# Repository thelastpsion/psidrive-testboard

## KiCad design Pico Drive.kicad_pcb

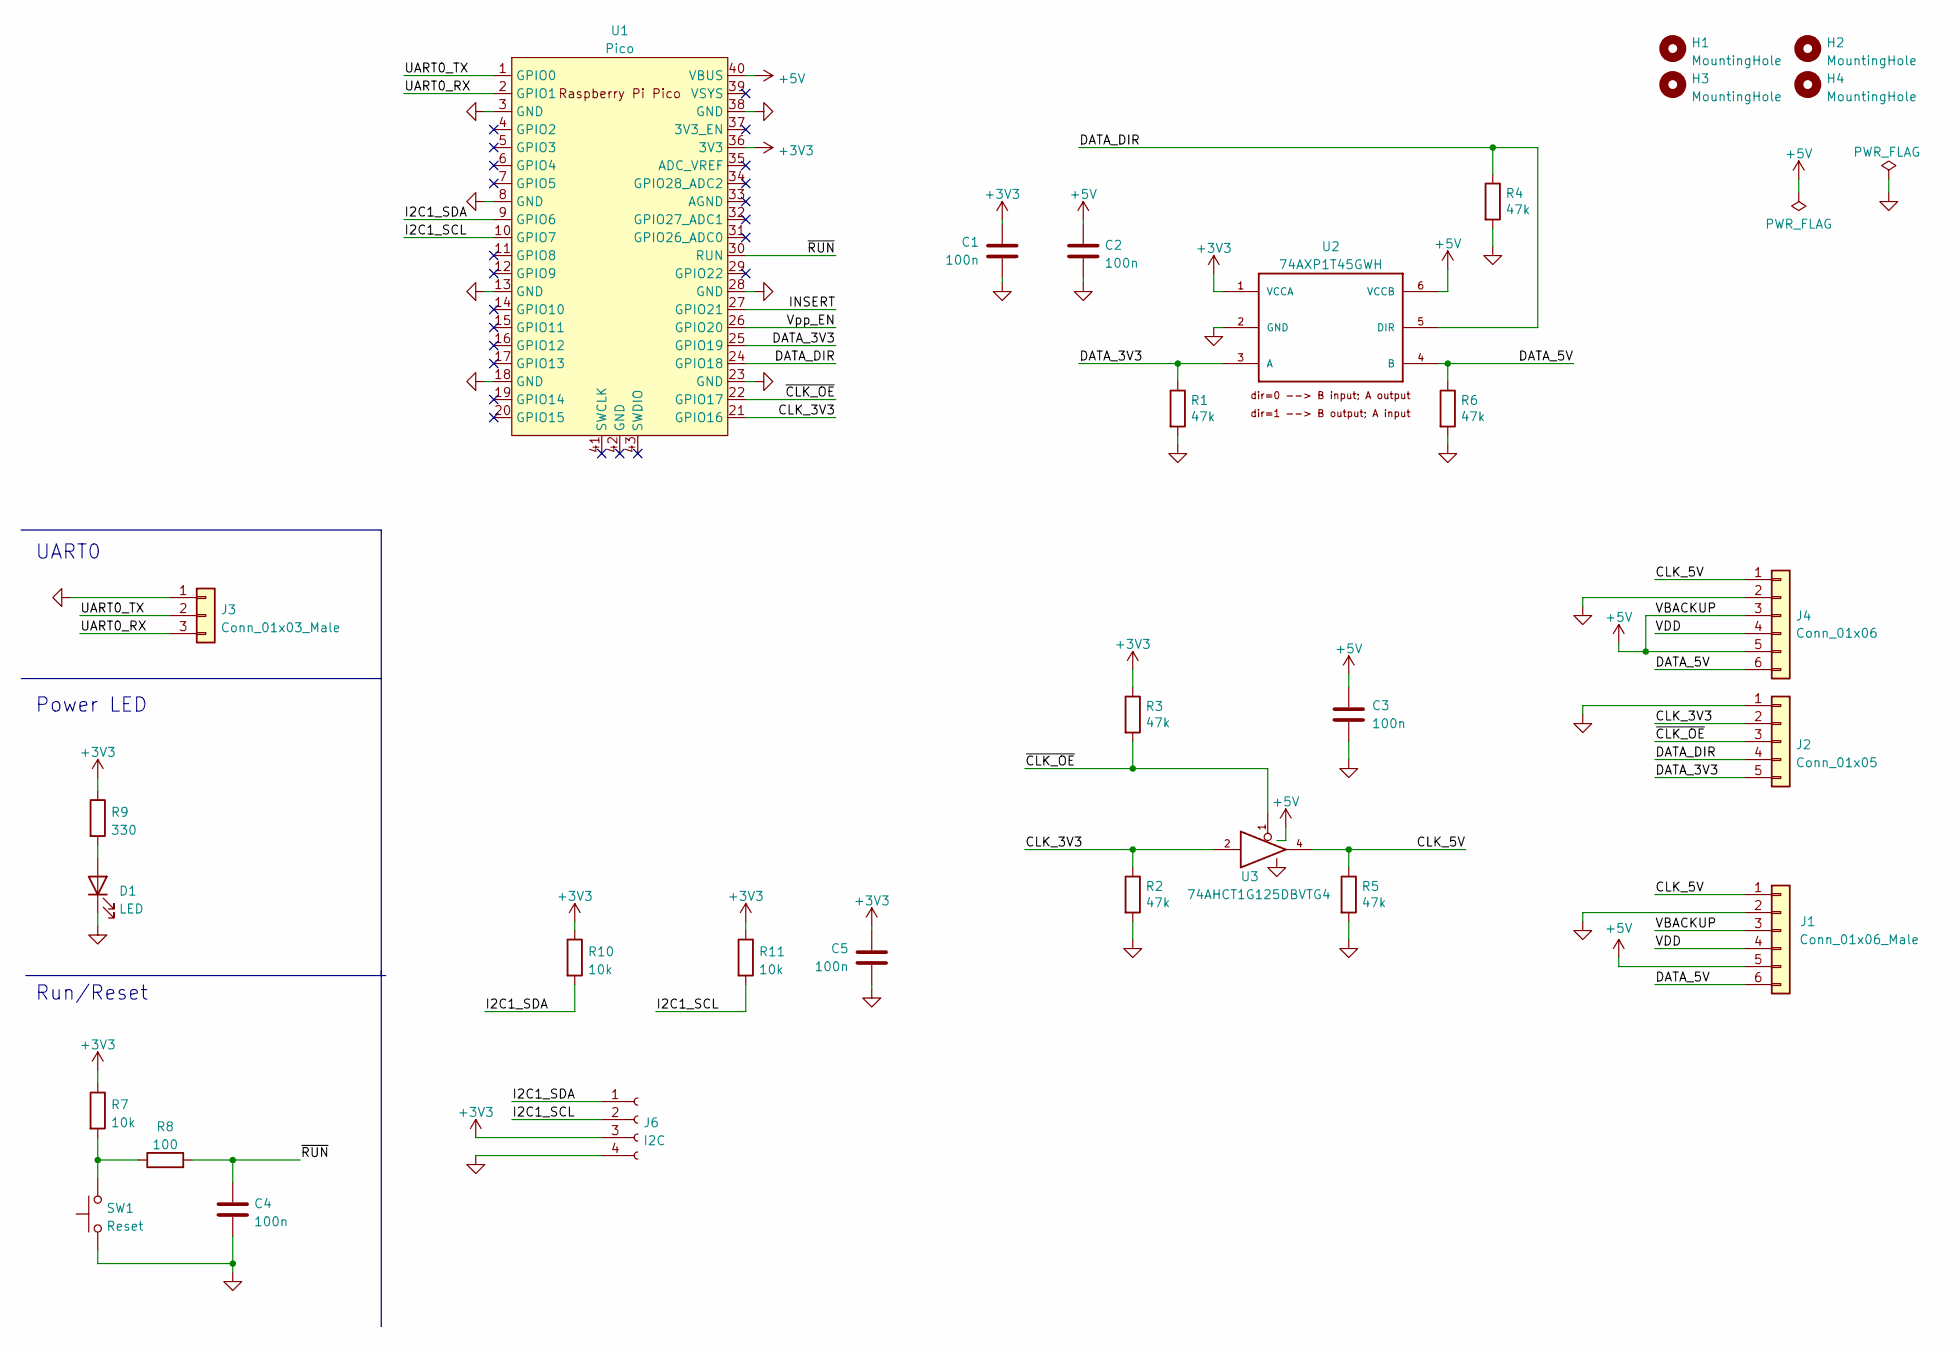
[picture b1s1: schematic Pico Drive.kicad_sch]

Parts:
C1, C2, C3, C4, C5: 100n; C_0805_2012Metric_Pad1.18x1.45mm_HandSolder
D1: LED; LED_D3.0mm_Clear
H1, H2, H3, H4: MountingHole; MountingHole_2.2mm_M2
J1: Conn_01x06_Male; PinHeader_1x06_P2.54mm_Vertical
J2: Conn_01x05; PinSocket_1x05_P2.54mm_Vertical
J3: Conn_01x03_Male; PinHeader_1x03_P2.54mm_Vertical
J4: Conn_01x06; PinSocket_1x06_P2.54mm_Vertical
J6: I2C; PinSocket_1x04_P2.54mm_Vertical
R1, R2, R3, R4, R5, R6: 47k; R_0805_2012Metric_Pad1.20x1.40mm_HandSolder
R7, R10, R11: 10k; R_0805_2012Metric_Pad1.20x1.40mm_HandSolder
R8: 100; R_0805_2012Metric_Pad1.20x1.40mm_HandSolder
R9: 330; R_0805_2012Metric_Pad1.20x1.40mm_HandSolder
SW1: Reset; SW_PUSH_6mm_H5mm
U1: Pico; RPi_Pico_SMD_TH
U2: 74AXP1T45GWH; SOT-363_SC-70-6_Handsoldering; MFR_PN 74AXP1T45GWH; DIGIKEY 1727-74AXP1T45GWHCT-ND
U3: 74AHCT1G125DBVTG4; TSOT-23-5

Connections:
+3V3: C1.1, C5.1, J6.3, R3.1, R7.1, R9.1, R10.1, R11.1, U1.36 (3V3), U2.1 (VCCA)
+5V: C2.1, C3.1, J1.3, J1.5, J4.3, J4.5, U1.40 (VBUS), U2.6 (VCCB), U3.5 (VCC)
/CLK_3V3: J2.2, R2.1, U1.21 (GPIO16), U3.2
/CLK_5V: J1.1, J4.1, R5.1, U3.4
/DATA_3V3: J2.5, R1.1, U1.25 (GPIO19), U2.3 (A)
/DATA_5V: J1.6, J4.6, R6.1, U2.4 (B)
/DATA_DIR: J2.4, R4.1, U1.24 (GPIO18), U2.5 (DIR)
/I2C1_SCL: J6.2, R11.2, U1.10 (GPIO7)
/I2C1_SDA: J6.1, R10.2, U1.9 (GPIO6)
/INSERT: U1.27 (GPIO21)
/UART0_RX: J3.3, U1.2 (GPIO1)
/UART0_TX: J3.2, U1.1 (GPIO0)
/VDD: J1.4, J4.4
/Vpp_EN: U1.26 (GPIO20)
/~CLK_OE: J2.3, R3.2, U1.22 (GPIO17), U3.1
/~RUN: C4.1, R8.2, U1.30 (RUN)
GND: C1.2, C2.2, C3.2, C4.2, C5.2, D1.1 (K), J1.2, J2.1, J3.1, J4.2, J6.4, R1.2, R2.2, R4.2, R5.2, R6.2, SW1.1, U1.3 (GND), U1.8 (GND), U1.13 (GND), U1.18 (GND), U1.23 (GND), U1.28 (GND), U1.38 (GND), U2.2 (GND), U3.3 (GND)
unnamed: D1.2 (A), R9.2
unnamed: R7.2, R8.1, SW1.2

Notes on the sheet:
Power LED
Run/Reset
UART0

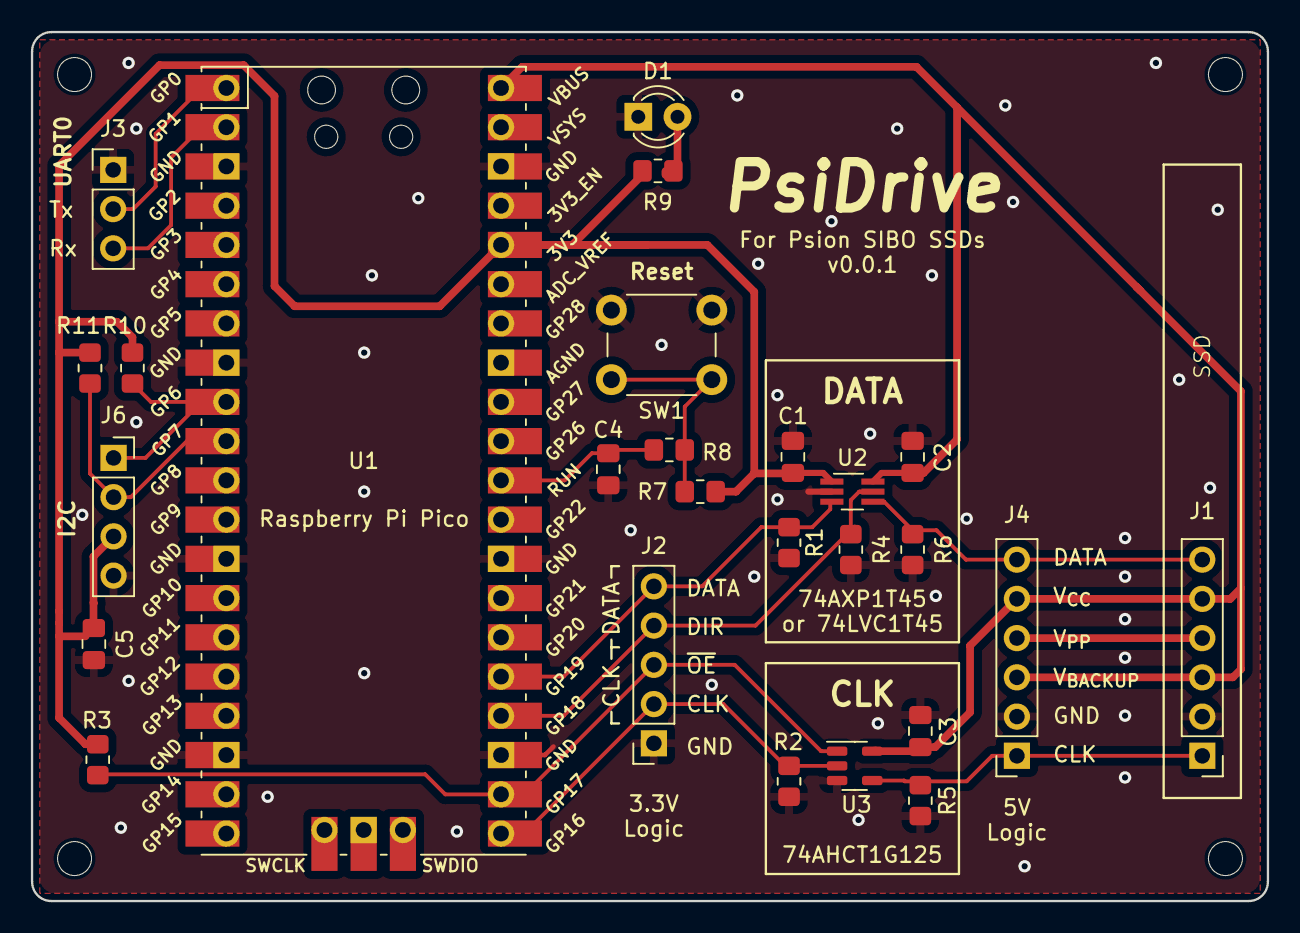
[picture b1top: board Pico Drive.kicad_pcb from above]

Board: 2 copper layers, 80.0 x 56.2 mm, 30 parts (0 on the bottom side), 17 nets.

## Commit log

2022-08-04 Modified .gitignore
2022-08-04 Replaced .gitignore with the one from the gitignore repo
2022-08-04 First proper commit
2022-08-04 Rotated CLK and DATA on PCB
2022-08-04 Added space for Vpp circuitry
2022-08-09 Shifted bits around, ran power, added cutout
2023-02-02 Cleared out old traces ready for overhaul
2023-02-02 Swapped some TH for SMDs, fixed caps, tidied
2023-02-09 Rotated and shrank the board, tidied stuff up
2023-08-06 Complete revamp, with routing.
2023-08-07 Moved R3, changed U2 for SOT363, various fixes
2023-08-08 Changed all 0402 components to 0805
2023-08-08 Swapped LED and reset switch, made more space
2023-08-08 Added pullups and decoupling for I2C
